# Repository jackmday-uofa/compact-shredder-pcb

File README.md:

# compact-shredder-pcb
PCB schematic and design for the Compact Shredder Design Version 2

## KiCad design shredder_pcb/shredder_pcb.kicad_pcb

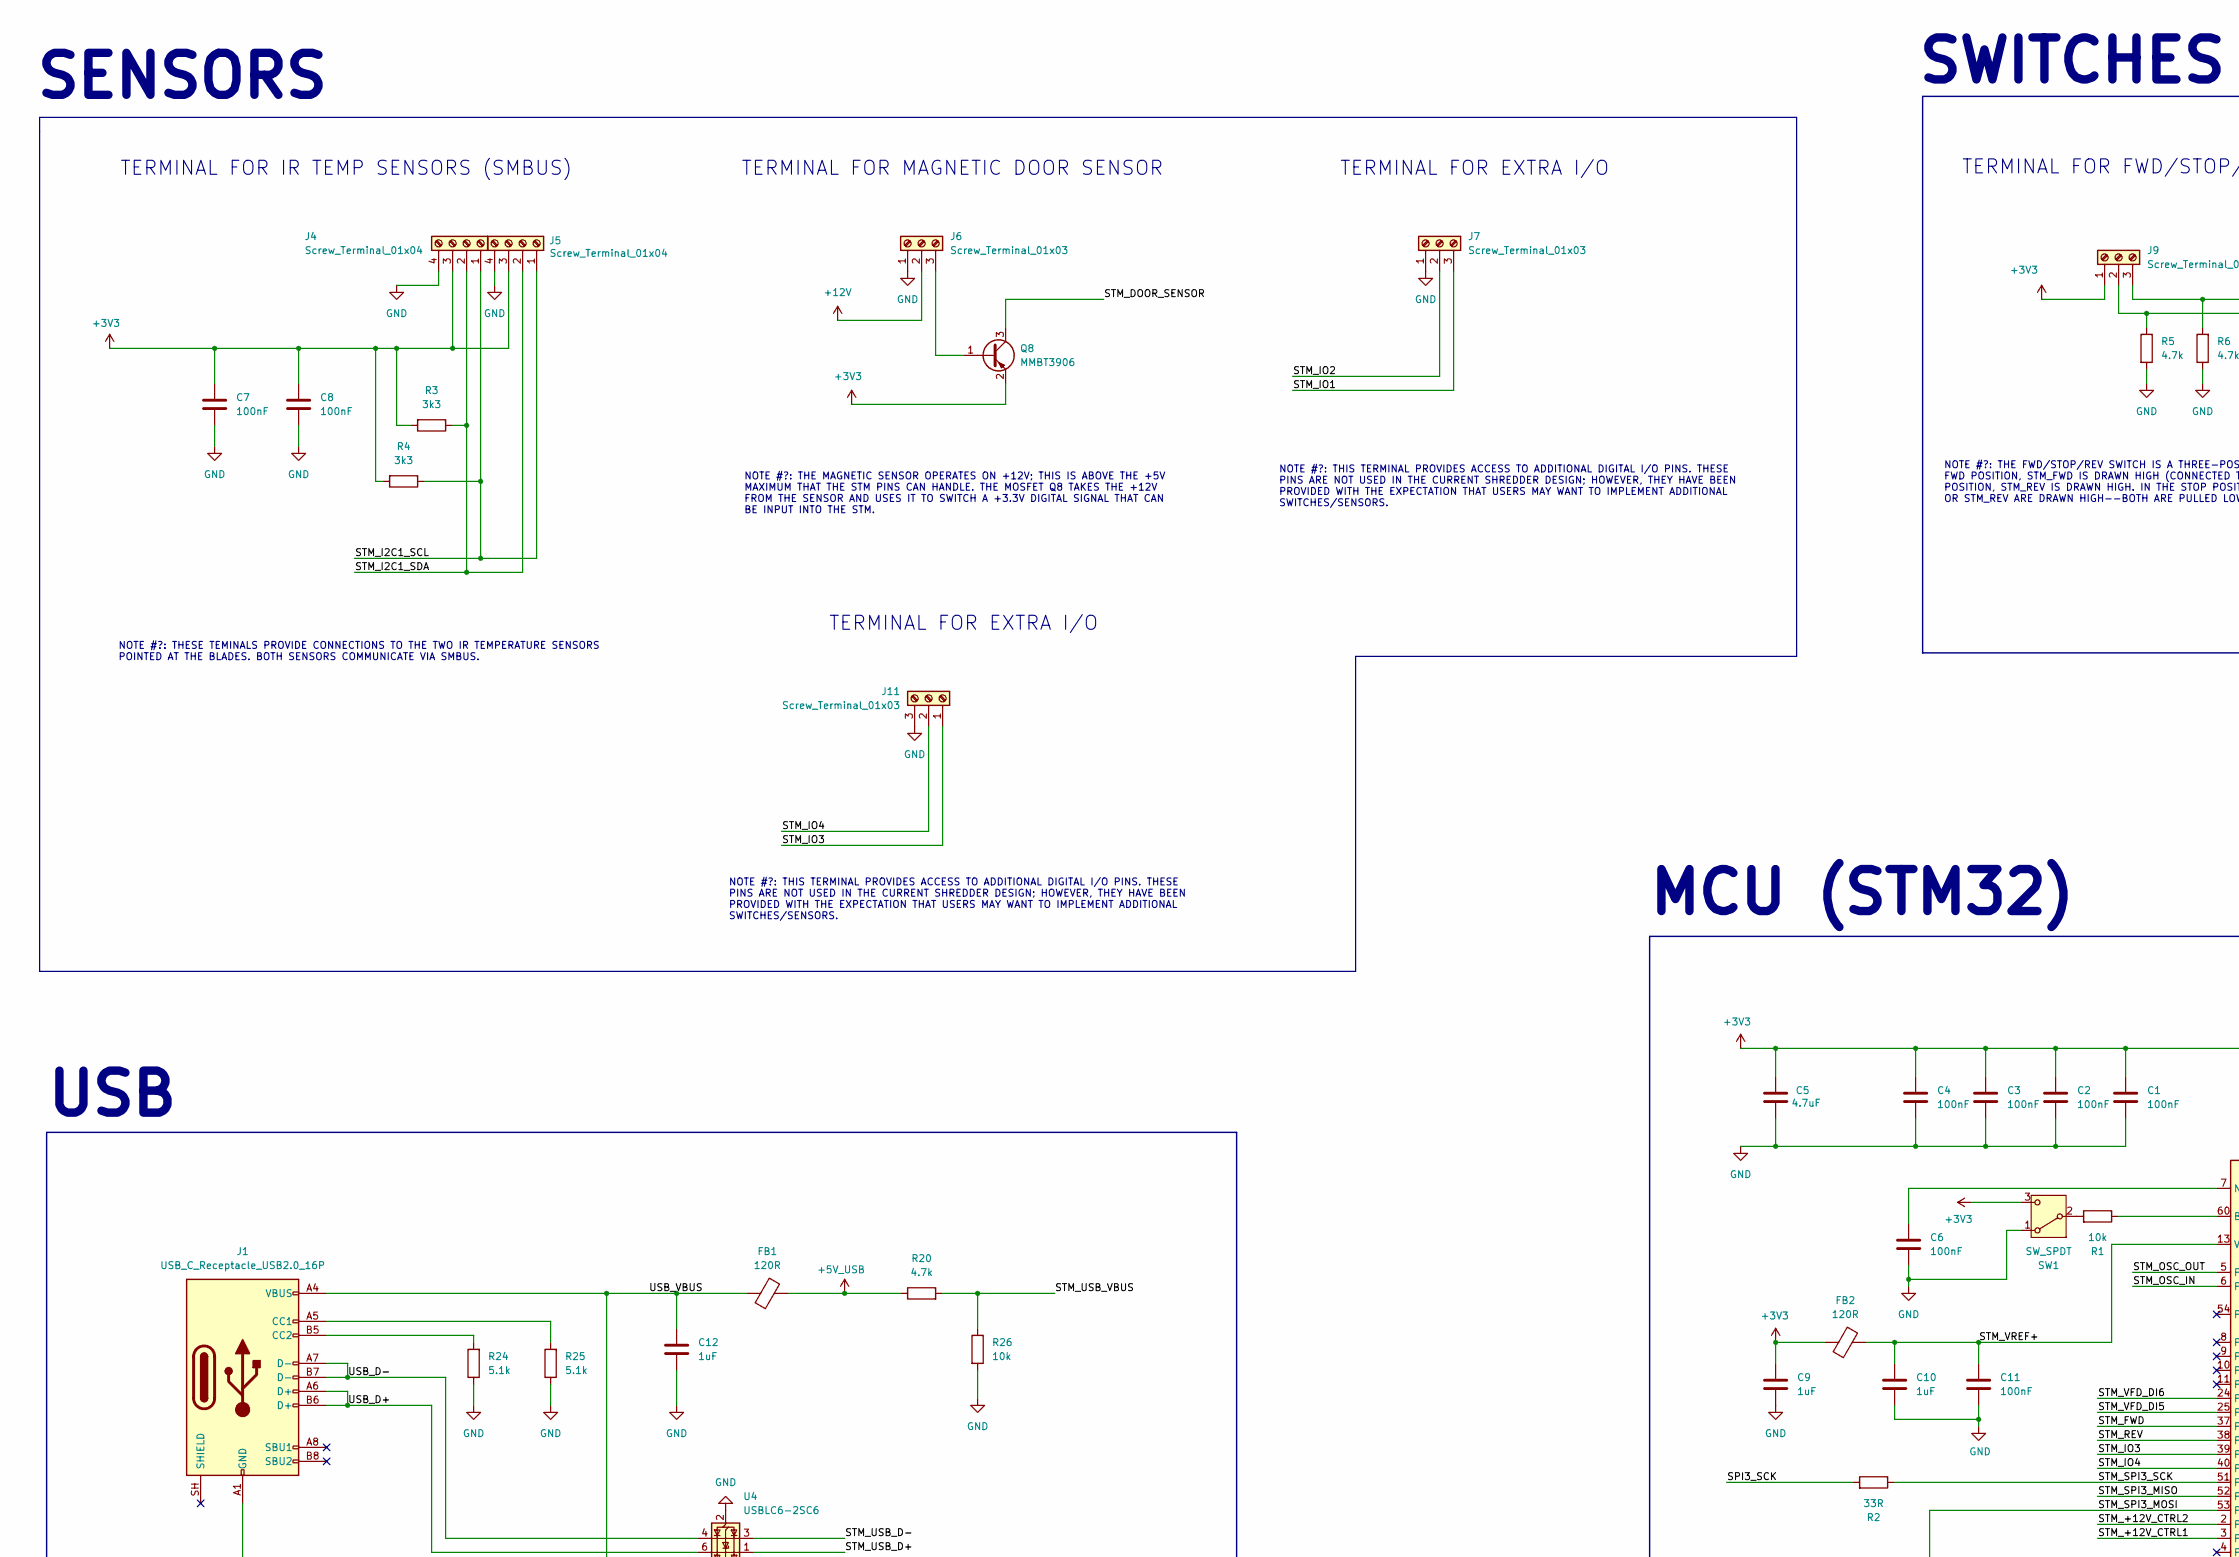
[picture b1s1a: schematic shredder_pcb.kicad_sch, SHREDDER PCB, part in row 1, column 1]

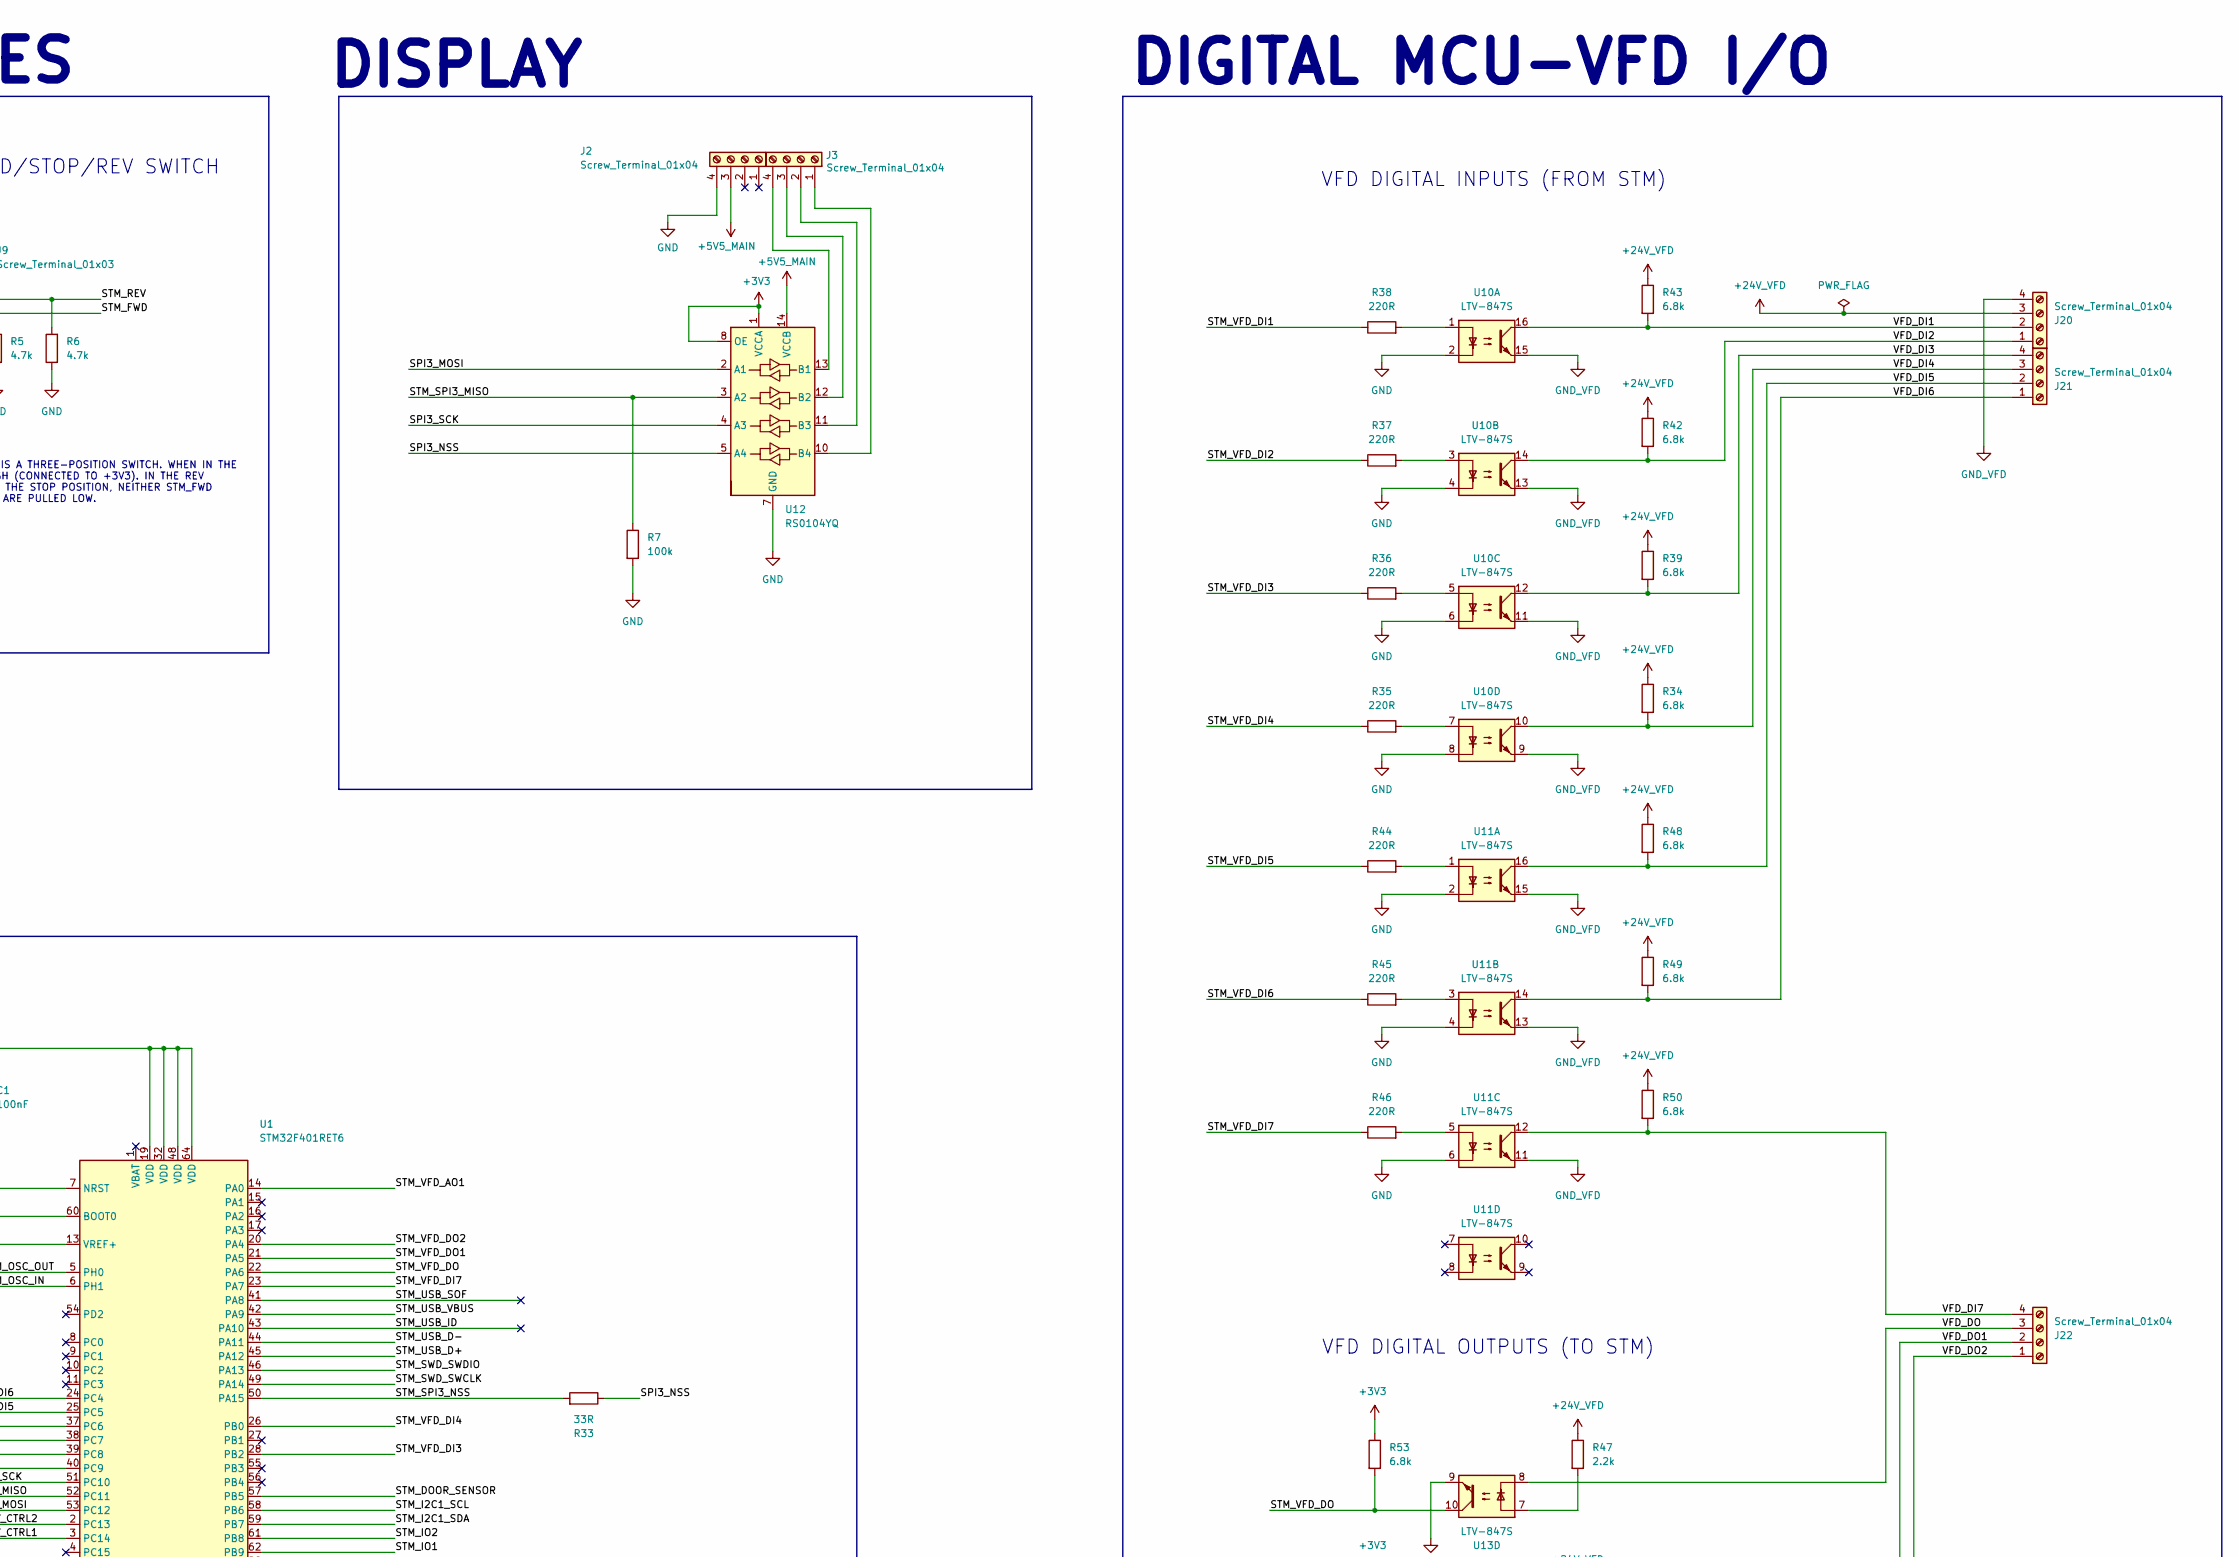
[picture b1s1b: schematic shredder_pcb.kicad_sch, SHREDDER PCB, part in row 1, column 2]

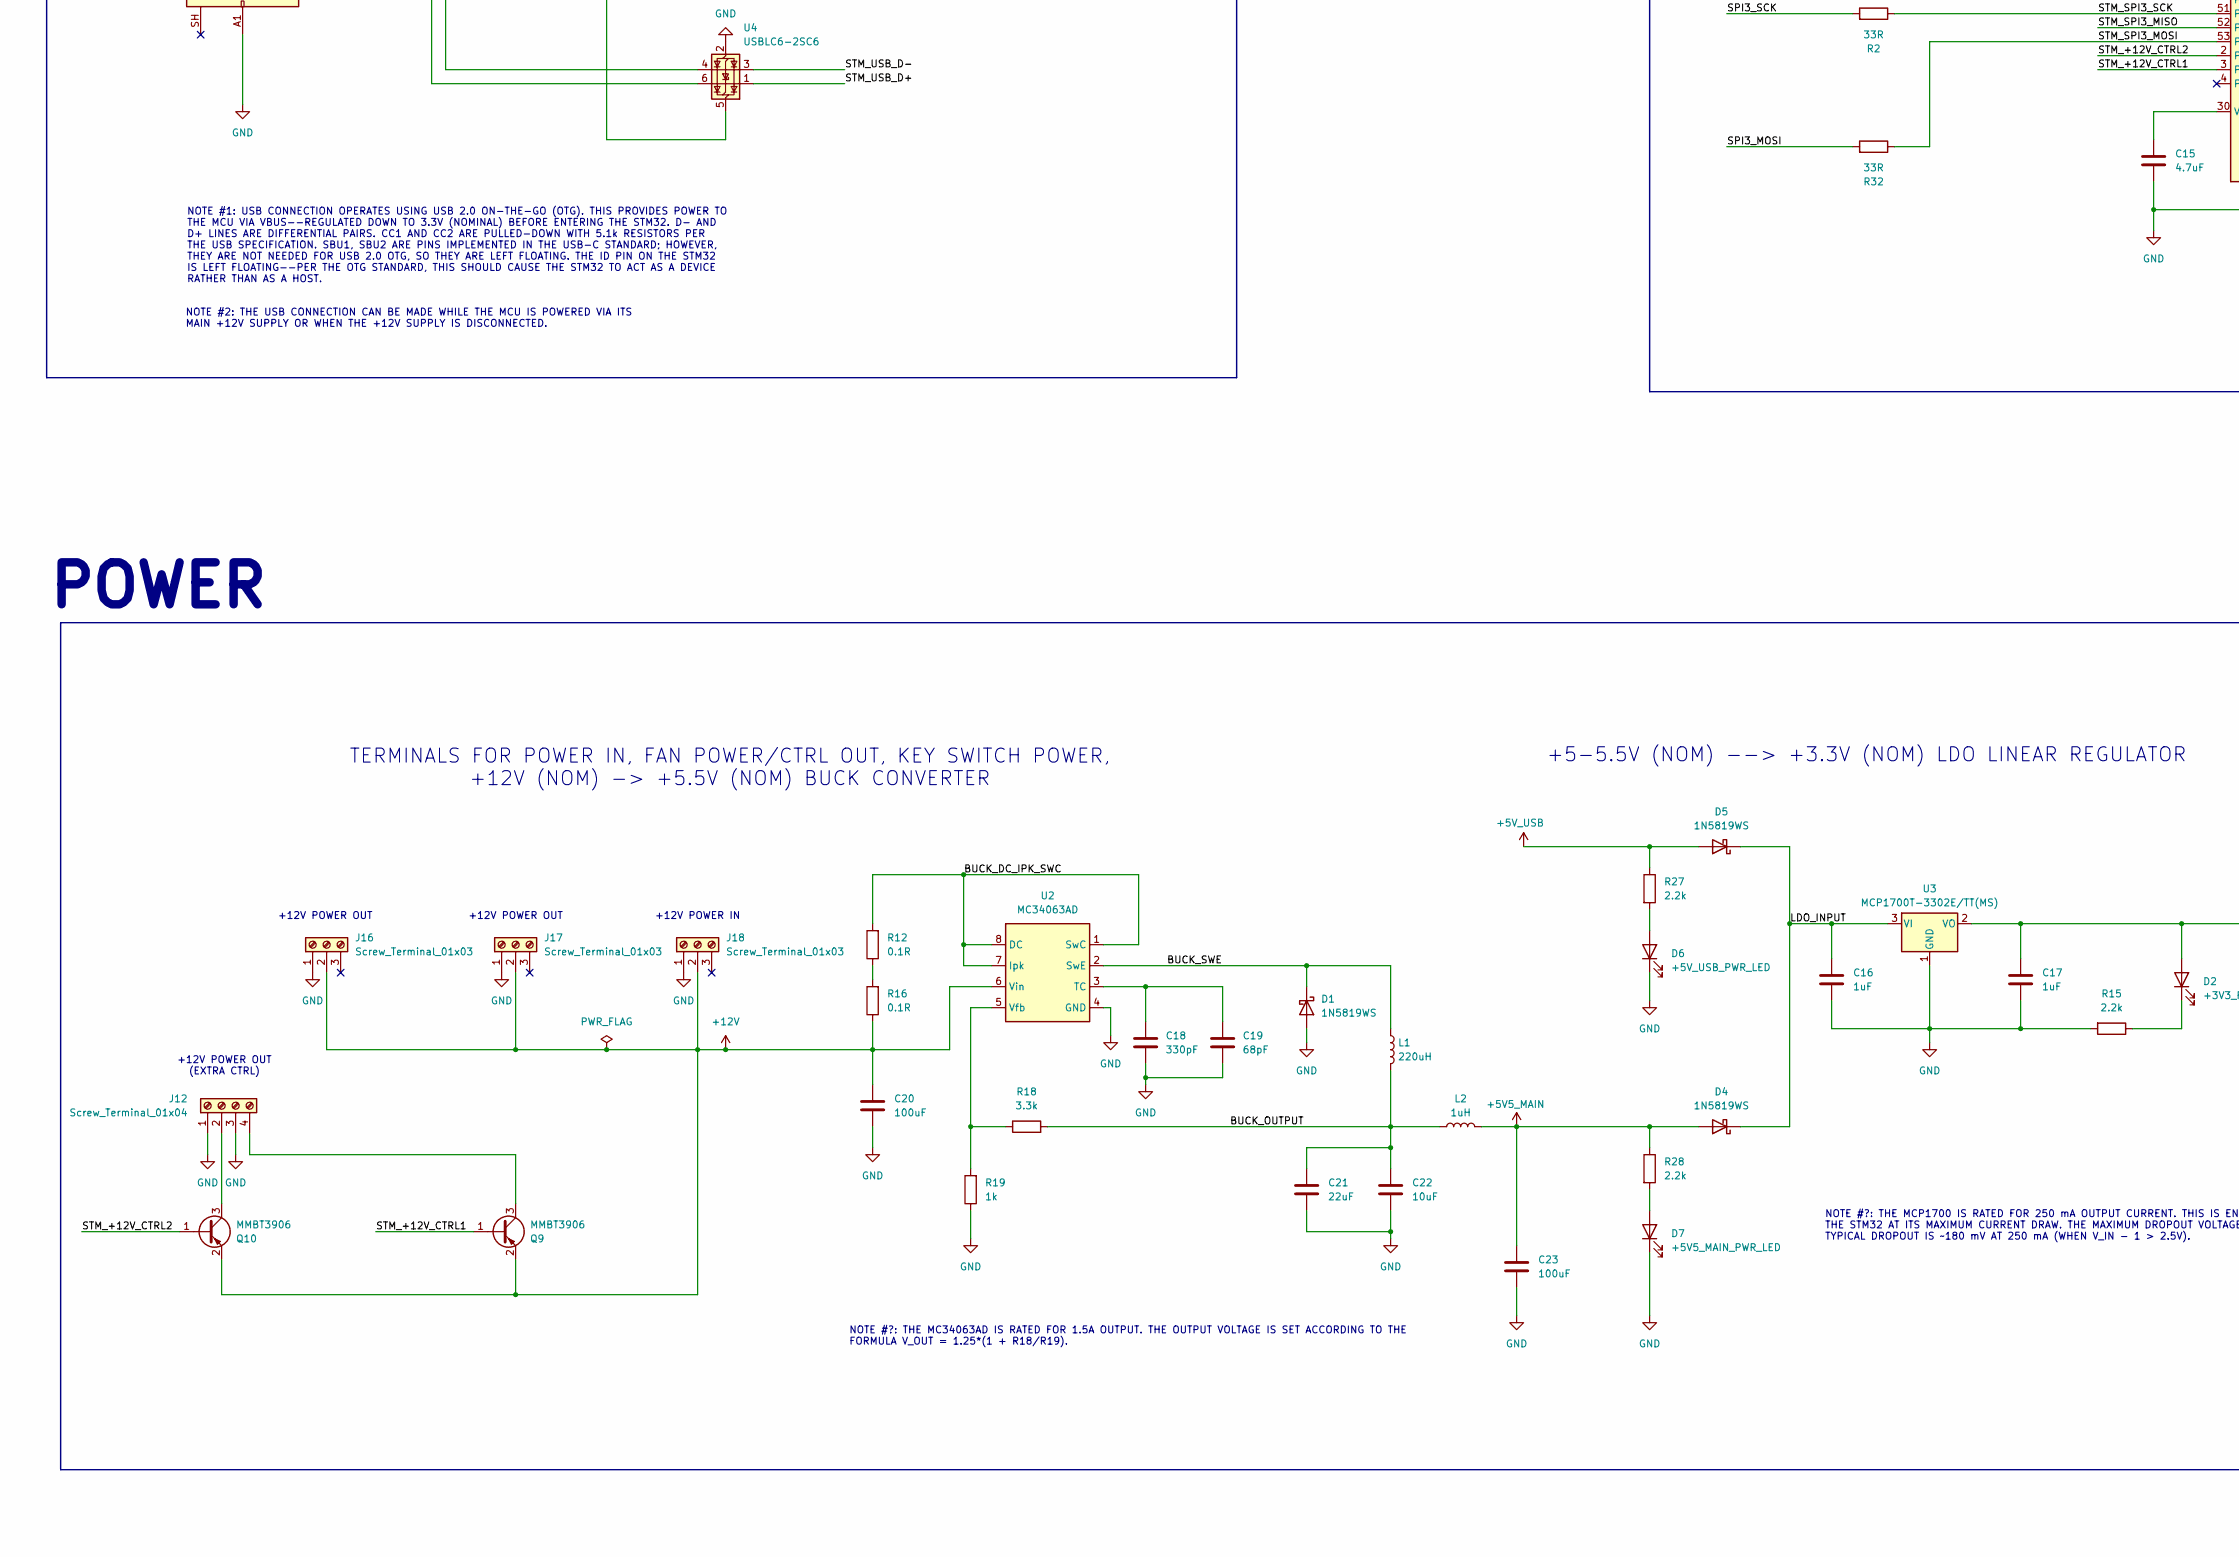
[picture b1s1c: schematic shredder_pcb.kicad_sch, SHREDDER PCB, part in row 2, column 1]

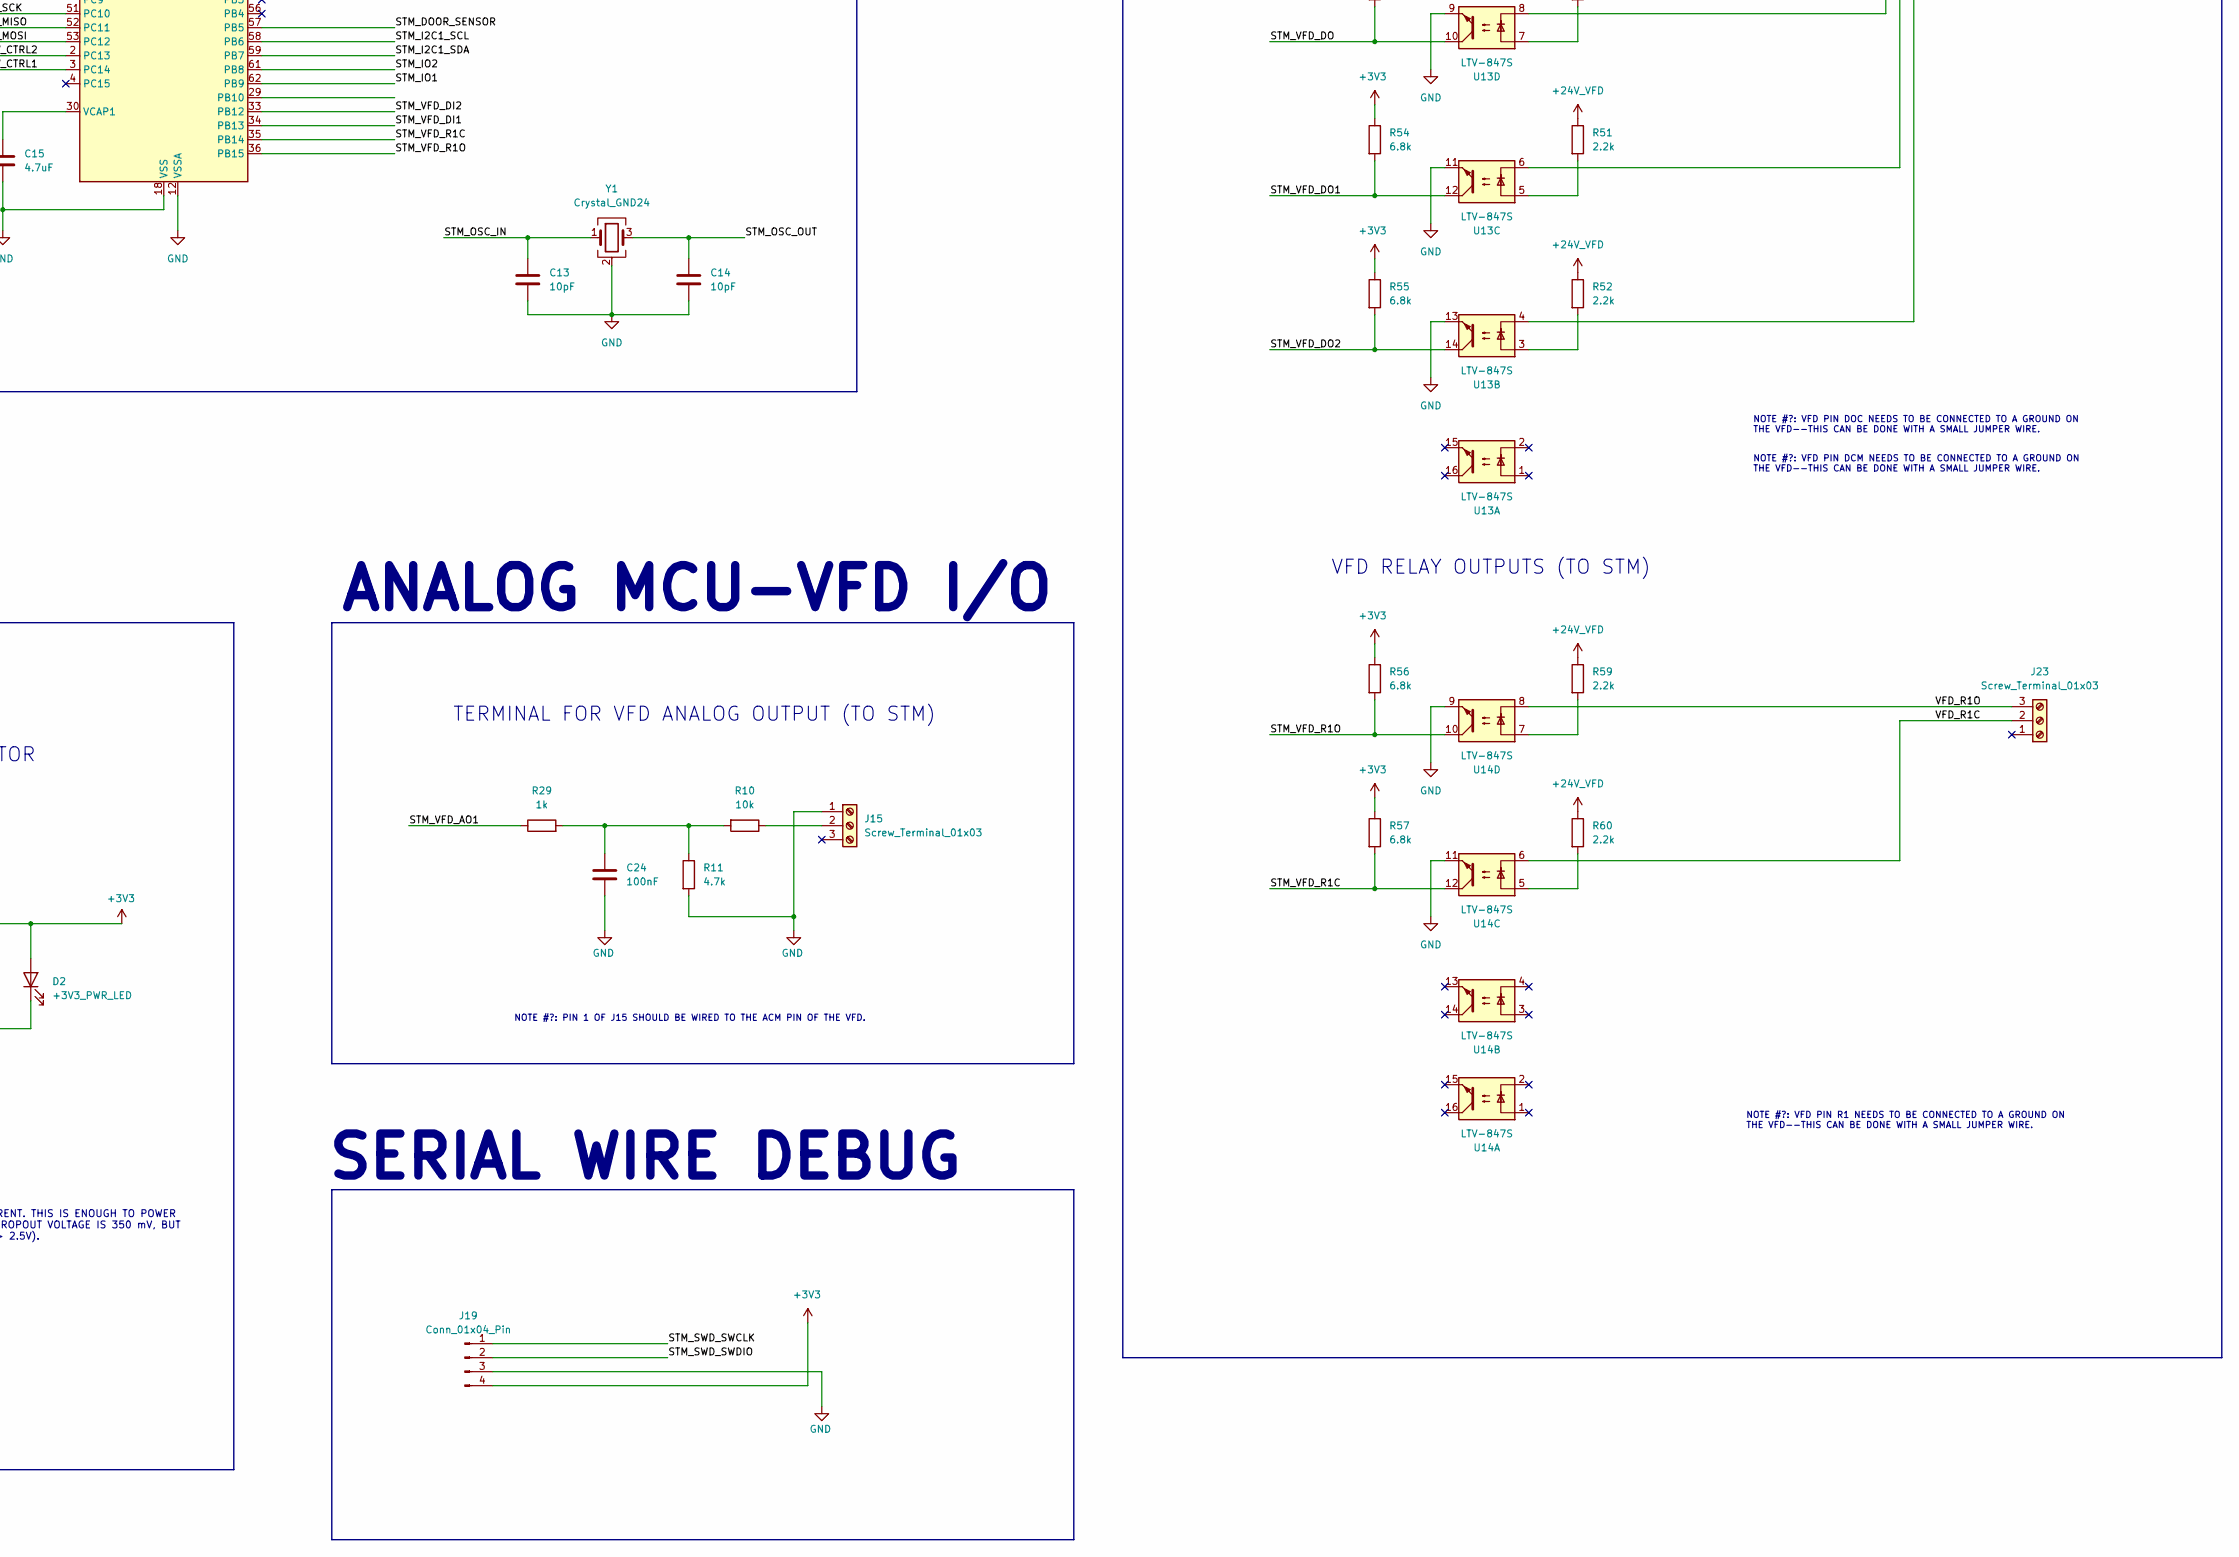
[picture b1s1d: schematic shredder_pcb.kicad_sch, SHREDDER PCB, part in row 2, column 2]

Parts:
C1, C2, C3, C4, C6, C7, C8, C11, C24: 100nF; C_0805_2012Metric
C5, C15: 4.7uF; C_0805_2012Metric
C9, C10, C12, C16, C17: 1uF; C_0805_2012Metric
C13, C14: 10pF; C_0603_1608Metric
C18: 330pF; C_0603_1608Metric
C19: 68pF; C_0603_1608Metric
C20, C23: 100uF; C_1206_3216Metric
C21: 22uF; C_1206_3216Metric
C22: 10uF; C_0805_2012Metric
D1, D4, D5: 1N5819WS; D_SOD-323
D2: +3V3_PWR_LED; LED_0603_1608Metric
D6: +5V_USB_PWR_LED; LED_0603_1608Metric
D7: +5V5_MAIN_PWR_LED; LED_0603_1608Metric
FB1, FB2: 120R; L_0805_2012Metric
J1: USB_C_Receptacle_USB2.0_16P; USB_C_Receptacle_GCT_USB4110
J2, J3, J4, J5, J12, J20, J21, J22: Screw_Terminal_01x04; DB301V-5.0_1x4P
J6, J7, J9, J11, J15, J16, J17, J18, J23: Screw_Terminal_01x03; KF301-5.0_1x3P
J19: Conn_01x04_Pin; PinHeader_1x04_P2.54mm_Vertical
L1: 220uH; L_1210_3225Metric
L2: 1uH; L_0805_2012Metric
Q8, Q9, Q10: MMBT3906; SOT-23-3
R1, R10, R26: 10k; R_0603_1608Metric
R2, R32, R33: 33R; R_0805_2012Metric
R3, R4: 3k3; R_0603_1608Metric
R5, R6, R11, R20: 4.7k; R_0603_1608Metric
R7: 100k; R_0603_1608Metric
R12, R16: 0.1R; R_1206_3216Metric
R15, R27, R28, R47, R51, R52, R59, R60: 2.2k; R_0603_1608Metric
R18: 3.3k; R_0603_1608Metric
R19, R29: 1k; R_0603_1608Metric
R24, R25: 5.1k; R_1206_3216Metric
R34, R39, R42, R43, R48, R49, R50, R53, R54, R55, R56, R57: 6.8k; R_0603_1608Metric
R35, R36, R37, R38, R44, R45, R46: 220R; R_0603_1608Metric
SW1: SW_SPDT; SW_SPDT_Shouhan_MSK12C02
U1: STM32F401RET6; LQFP-64_10x10mm_P0.5mm
U2: MC34063AD; SOIC-8_3.9x4.9mm_P1.27mm
U3: MCP1700T-3302E/TT(MS); SOT-23
U4: USBLC6-2SC6; SOT-23-6
U10, U11, U13, U14: LTV-847S; SMDIP-16_W9.53mm
U12: RS0104YQ; TSSOP-14_4.4x5mm_P0.65mm
Y1: Crystal_GND24; Crystal_SMD_3225-4Pin_3.2x2.5mm

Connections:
+3V3: C1.1, C2.1, C3.1, C4.1, C5.1, C7.1, C8.1, C9.1, C17.1, D2.2 (A), FB2.1, J4.3, J5.3, J9.1, J19.4, Q8.2 (E), R3.2, R4.2, R53.1, R54.1, R55.1, R56.1, R57.1, SW1.3 (C), U1.19 (VDD), U1.32 (VDD), U1.48 (VDD), U1.64 (VDD), U3.2 (VO), U12.1 (VCCA), U12.8 (OE)
+5V5_MAIN: C23.2, D4.2 (A), J2.3, L2.2, R28.1, U12.14 (VCCB)
+5V_USB: D5.2 (A), FB1.2, R20.1, R27.1
+12V: C20.2, J6.2, J16.2, J17.2, J18.2, Q9.2 (E), Q10.2 (E), R16.1, U2.6 (Vin)
+24V_VFD: J20.3, R34.1, R39.1, R42.1, R43.1, R47.1, R48.1, R49.1, R50.1, R51.1, R52.1, R59.1, R60.1
/Root/BUCK_DC_IPK_SWC: R12.2, U2.1 (SwC), U2.7 (Ipk), U2.8 (DC)
/Root/BUCK_OUTPUT: C21.2, C22.2, L1.2, L2.1, R18.2
/Root/BUCK_SWE: D1.1 (K), L1.1, U2.2 (SwE)
/Root/LDO_INPUT: C16.1, D4.1 (K), D5.1 (K), U3.3 (VI)
/Root/SPI3_MOSI: R32.2, U12.2 (A1)
/Root/SPI3_NSS: R33.1, U12.5 (A4)
/Root/SPI3_SCK: R2.2, U12.4 (A3)
/Root/STM_+12V_CTRL1: Q9.1 (B), U1.3 (PC14)
/Root/STM_+12V_CTRL2: Q10.1 (B), U1.2 (PC13)
/Root/STM_DOOR_SENSOR: Q8.3 (C), U1.57 (PB5)
/Root/STM_FWD: J9.2, R5.1, U1.37 (PC6)
/Root/STM_I2C1_SCL: J4.1, J5.1, R4.1, U1.58 (PB6)
/Root/STM_I2C1_SDA: J4.2, J5.2, R3.1, U1.59 (PB7)
/Root/STM_IO1: J7.3, U1.62 (PB9)
/Root/STM_IO2: J7.2, U1.61 (PB8)
/Root/STM_IO3: J11.1, U1.39 (PC8)
/Root/STM_IO4: J11.2, U1.40 (PC9)
/Root/STM_OSC_IN: C13.1, U1.6 (PH1), Y1.1
/Root/STM_OSC_OUT: C14.1, U1.5 (PH0), Y1.3
/Root/STM_REV: J9.3, R6.2, U1.38 (PC7)
/Root/STM_SPI3_MISO: R7.1, U1.52 (PC11), U12.3 (A2)
/Root/STM_SPI3_MOSI: R32.1, U1.53 (PC12)
/Root/STM_SPI3_NSS: R33.2, U1.50 (PA15)
/Root/STM_SPI3_SCK: R2.1, U1.51 (PC10)
/Root/STM_SWD_SWCLK: J19.1, U1.49 (PA14)
/Root/STM_SWD_SWDIO: J19.2, U1.46 (PA13)
/Root/STM_USB_D+: U1.45 (PA12), U4.1 (I/O1)
/Root/STM_USB_D-: U1.44 (PA11), U4.3 (I/O2)
/Root/STM_USB_ID: U1.43 (PA10)
/Root/STM_USB_SOF: U1.41 (PA8)
/Root/STM_USB_VBUS: R20.2, R26.1, U1.42 (PA9)
/Root/STM_VFD_AO1: R29.1, U1.14 (PA0)
/Root/STM_VFD_DI1: R38.1, U1.34 (PB13)
/Root/STM_VFD_DI2: R37.1, U1.33 (PB12)
/Root/STM_VFD_DI3: R36.1, U1.28 (PB2)
/Root/STM_VFD_DI4: R35.1, U1.26 (PB0)
/Root/STM_VFD_DI5: R44.1, U1.25 (PC5)
/Root/STM_VFD_DI6: R45.1, U1.24 (PC4)
/Root/STM_VFD_DI7: R46.1, U1.23 (PA7)
/Root/STM_VFD_DO: R53.2, U1.22 (PA6), U13.10
/Root/STM_VFD_DO1: R54.2, U1.21 (PA5), U13.12
/Root/STM_VFD_DO2: R55.2, U1.20 (PA4), U13.14
/Root/STM_VFD_R1C: R57.2, U1.35 (PB14), U14.12
/Root/STM_VFD_R1O: R56.2, U1.36 (PB15), U14.10
/Root/STM_VREF+: C10.1, C11.1, FB2.2, U1.13 (VREF+)
/Root/USB_D+: J1.A6 (D+), J1.B6 (D+), U4.6 (I/O1)
/Root/USB_D-: J1.A7 (D-), J1.B7 (D-), U4.4 (I/O2)
/Root/USB_VBUS: C12.1, FB1.1, J1.A4 (VBUS), J1.A9 (VBUS), J1.B4 (VBUS), J1.B9 (VBUS), U4.5 (VBUS)
/Root/VFD_DI1: J20.2, R43.2, U10.16
/Root/VFD_DI2: J20.1, R42.2, U10.14
/Root/VFD_DI3: J21.4, R39.2, U10.12
/Root/VFD_DI4: J21.3, R34.2, U10.10
/Root/VFD_DI5: J21.2, R48.2, U11.16
/Root/VFD_DI6: J21.1, R49.2, U11.14
/Root/VFD_DI7: J22.4, R50.2, U11.12
/Root/VFD_DO: J22.3, U13.8
/Root/VFD_DO1: J22.2, U13.6
/Root/VFD_DO2: J22.1, U13.4
/Root/VFD_R1C: J23.2, U14.6
/Root/VFD_R1O: J23.3, U14.8
GND: C1.2, C2.2, C3.2, C4.2, C5.2, C6.2, C7.2, C8.2, C9.2, C10.2, C11.2, C12.2, C13.2, C14.2, C15.2, C16.2, C17.2, C18.1, C19.1, C20.1, C21.1, C22.1, C23.1, C24.2, D1.2 (A), D6.1 (K), D7.1 (K), J1.A1 (GND), J1.A12 (GND), J1.B1 (GND), J1.B12 (GND), J2.4, J4.4, J5.4, J6.1, J7.1, J11.3, J12.1, J12.3, J15.1, J16.1, J17.1, J18.1, J19.3, R5.2, R6.1, R7.2, R11.2, R15.2, R19.1, R24.1, R25.1, R26.2, SW1.1 (A), U1.12 (VSSA), U1.18 (VSS), U1.31 (VSS), U1.47 (VSS), U1.63 (VSS), U2.4 (GND), U3.1 (GND), U4.2 (GND), U10.2, U10.4, U10.6, U10.8, U11.2, U11.4, U11.6, U12.7 (GND), U13.9, U13.11, U13.13, U14.9, U14.11, Y1.2 (G), Y1.4 (G)
GND_VFD: J20.4, U10.9, U10.11, U10.13, U10.15, U11.11, U11.13, U11.15
unnamed: C24.1, R10.2, R11.1, R29.2
unnamed: D2.1 (K), R15.1
unnamed: D6.2 (A), R27.2
unnamed: D7.2 (A), R28.2
unnamed: J1.A5 (CC1), R25.2
unnamed: J1.B5 (CC2), R24.2
unnamed: J3.1, U12.10 (B4)
unnamed: J3.2, U12.11 (B3)
unnamed: J3.3, U12.12 (B2)
unnamed: J3.4, U12.13 (B1)
unnamed: J6.3, Q8.1 (B)
unnamed: J12.2, Q10.3 (C)
unnamed: J12.4, Q9.3 (C)
unnamed: J15.2, R10.1
unnamed: R12.1, R16.2
unnamed: R35.2, U10.7
unnamed: R36.2, U10.5
unnamed: R37.2, U10.3
unnamed: R38.2, U10.1
unnamed: R44.2, U11.1
unnamed: R45.2, U11.3
unnamed: R46.2, U11.5
unnamed: R47.2, U13.7
unnamed: R51.2, U13.5
unnamed: R52.2, U13.3
unnamed: R59.2, U14.7
unnamed: R60.2, U14.5
unnamed: R1.2, SW1.2 (B)
unnamed: R1.1, U1.60 (BOOT0)
unnamed: C6.1, U1.7 (NRST)
unnamed: C15.1, U1.30 (VCAP1)
unnamed: C18.2, C19.2, U2.3 (TC)
unnamed: R18.1, R19.2, U2.5 (Vfb)

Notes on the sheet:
+12V POWER IN
TERMINAL FOR EXTRA I/O
VFD DIGITAL OUTPUTS (TO STM)
DIGITAL MCU-VFD I/O
TERMINAL FOR MAGNETIC DOOR SENSOR
+5-5.5V (NOM) --> +3.3V (NOM) LDO LINEAR REGULATOR
NOTE #?: THESE TEMINALS PROVIDE CONNECTIONS TO THE TWO IR TEMPERATURE SENSORS POINTED AT THE BLADES. BOTH SENSORS COMMUNICATE VIA SMBUS.
SERIAL WIRE DEBUG
TERMINAL FOR VFD ANALOG OUTPUT (TO STM)
+12V POWER OUT
VFD RELAY OUTPUTS (TO STM)
NOTE #?: THE MAGNETIC SENSOR OPERATES ON +12V; THIS IS ABOVE THE +5V MAXIMUM THAT THE STM PINS CAN HANDLE. THE MOSFET Q8 TAKES THE +12V FROM THE SENSOR AND USES IT TO SWITCH A +3.3V DIGITAL SIGNAL THAT CAN BE INPUT INTO THE STM.
NOTE #?: VFD PIN DOC NEEDS TO BE CONNECTED TO A GROUND ON THE VFD--THIS CAN BE DONE WITH A SMALL JUMPER WIRE.
SENSORS
TERMINALS FOR POWER IN, FAN POWER/CTRL OUT, KEY SWITCH POWER, +12V (NOM) -> +5.5V (NOM) BUCK CONVERTER
MCU (STM32)
NOTE #?: THIS TERMINAL PROVIDES ACCESS TO ADDITIONAL DIGITAL I/O PINS. THESE PINS ARE NOT USED IN THE CURRENT SHREDDER DESIGN; HOWEVER, THEY HAVE BEEN PROVIDED WITH THE EXPECTATION THAT USERS MAY WANT TO IMPLEMENT ADDITIONAL SWITCHES/SENSORS.
ANALOG MCU-VFD I/O
NOTE #2: THE USB CONNECTION CAN BE MADE WHILE THE MCU IS POWERED VIA ITS MAIN +12V SUPPLY OR WHEN THE +12V SUPPLY IS DISCONNECTED.
DISPLAY
NOTE #?: VFD PIN R1 NEEDS TO BE CONNECTED TO A GROUND ON THE VFD--THIS CAN BE DONE WITH A SMALL JUMPER WIRE.
TERMINAL FOR FWD/STOP/REV SWITCH
USB
NOTE #1: USB CONNECTION OPERATES USING USB 2.0 ON-THE-GO (OTG). THIS PROVIDES POWER TO THE MCU VIA VBUS--REGULATED DOWN TO 3.3V (NOMINAL) BEFORE ENTERING THE STM32. D- AND D+ LINES ARE DIFFERENTIAL PAIRS. CC1 AND CC2 ARE PULLED-DOWN WITH 5.1k RESISTORS PER THE USB SPECIFICATION. SBU1, SBU2 ARE PINS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
VFD DIGITAL INPUTS (FROM STM)
NOTE #?: VFD PIN DCM NEEDS TO BE CONNECTED TO A GROUND ON THE VFD--THIS CAN BE DONE WITH A SMALL JUMPER WIRE.
+12V POWER OUT (EXTRA CTRL)
NOTE #?: THE FWD/STOP/REV SWITCH IS A THREE-POSITION SWITCH. WHEN IN THE FWD POSITION, STM_FWD IS DRAWN HIGH (CONNECTED TO +3V3). IN THE REV POSITION, STM_REV IS DRAWN HIGH. IN THE STOP POSITION, NEITHER STM_FWD OR STM_REV ARE DRAWN HIGH--BOTH ARE PULLED LOW.
NOTE #?: THE MC34063AD IS RATED FOR 1.5A OUTPUT. THE OUTPUT VOLTAGE IS SET ACCORDING TO THE FORMULA V_OUT = 1.25*(1 + R18/R19).
NOTE #?: PIN 1 OF J15 SHOULD BE WIRED TO THE ACM PIN OF THE VFD.
SWITCHES
POWER
TERMINAL FOR IR TEMP SENSORS (SMBUS)
NOTE #?: THE MCP1700 IS RATED FOR 250 mA OUTPUT CURRENT. THIS IS ENOUGH TO POWER THE STM32 AT ITS MAXIMUM CURRENT DRAW. THE MAXIMUM DROPOUT VOLTAGE IS 350 mV, BUT TYPICAL DROPOUT IS ~180 mV AT 250 mA (WHEN V_IN - 1 > 2.5V).

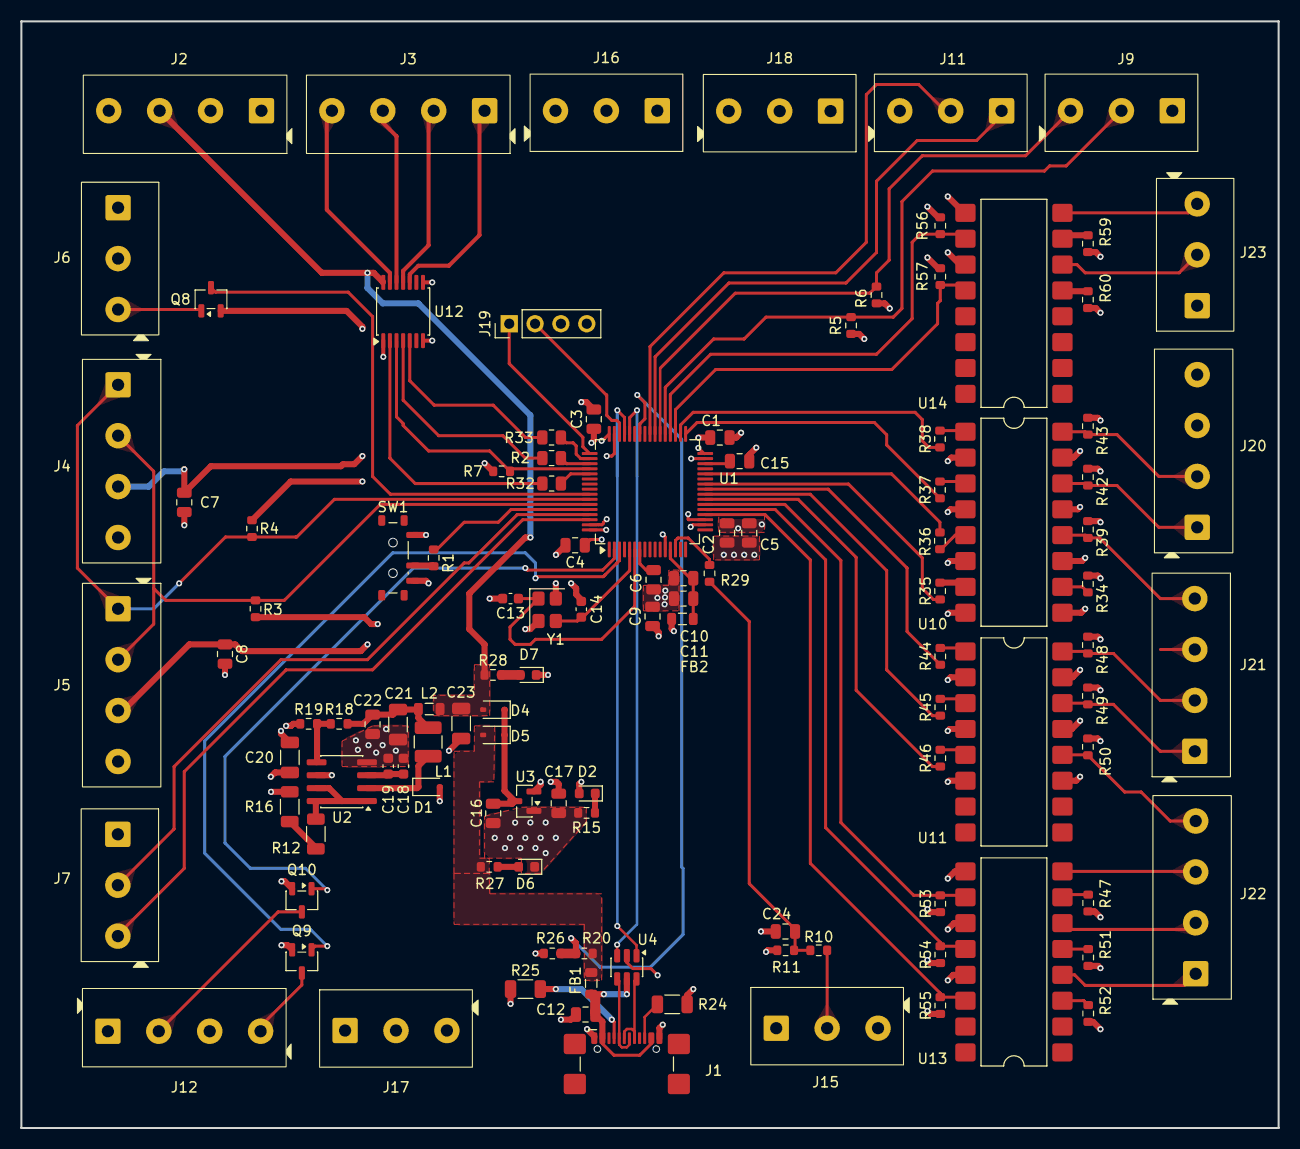
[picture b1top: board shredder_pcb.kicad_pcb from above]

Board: 4 copper layers, 123.5 x 108.7 mm, 114 parts (0 on the bottom side), 98 nets.

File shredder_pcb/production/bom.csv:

Designator,Footprint,Quantity,Value,LCSC Part #
"C1, C11, C2, C24, C3, C4, C6, C7, C8",0805,9,100nF,
"C10, C12, C16, C17, C9",0805,5,1uF,
"C13, C14",0603,2,10pF,
"C15, C5",0805,2,4.7uF,
C18,0603,1,330pF,
C19,0603,1,68pF,
"C20, C23",1206,2,100uF,
C21,1206,1,22uF,
C22,0805,1,10uF,
"D1, D4, D5",D_SOD-323,3,1N5819WS,
D2,0603,1,+3V3_PWR_LED,
D6,0603,1,+5V_USB_PWR_LED,
D7,0603,1,+5V5_MAIN_PWR_LED,
"FB1, FB2",0805,2,120R,
J1,USB_C_Receptacle_GCT_USB4110,1,USB_C_Receptacle_USB2.0_16P,
"J11, J15, J16, J17, J18, J23, J6, J7, J9",KF301-5.0_1x3P,9,Screw_Terminal_01x03,
"J12, J2, J20, J21, J22, J3, J4, J5",DB301V-5.0_1x4P,8,Screw_Terminal_01x04,
J19,PinHeader_1x04_P2.54mm_Vertical,1,Conn_01x04_Pin,
L1,1210,1,220uH,
L2,0805,1,1uH,
"Q10, Q8, Q9",SOT-23-3,3,MMBT3906,
"R1, R10, R26",0603,3,10k,
"R11, R20, R5, R6",0603,4,4.7k,
"R12, R16",1206,2,0.1R,
"R15, R27, R28, R47, R51, R52, R59, R60",0603,8,2.2k,
R18,0603,1,3.3k,
"R19, R29",0603,2,1k,
"R2, R32, R33",0805,3,33R,
"R24, R25",1206,2,5.1k,
"R3, R4",0603,2,3k3,
"R34, R39, R42, R43, R48, R49, R50, R53, R54, R55, R56, R57",0603,12,6.8k,
"R35, R36, R37, R38, R44, R45, R46",0603,7,220R,
R7,0603,1,100k,
SW1,SW_SPDT_Shouhan_MSK12C02,1,SW_SPDT,
U1,LQFP-64_10x10mm_P0.5mm,1,STM32F401RET6,
"U10, U11, U13, U14",SMDIP-16_W9.53mm,4,LTV-847S,
U12,TSSOP-14_4.4x5mm_P0.65mm,1,RS0104YQ,
U2,SOIC-8_3.9x4.9mm_P1.27mm,1,MC34063AD,
U3,SOT-23,1,MCP1700T-3302E/TT(MS),
U4,SOT-23-6,1,USBLC6-2SC6,
Y1,Crystal_SMD_3225-4Pin_3.2x2.5mm,1,Crystal_GND24,

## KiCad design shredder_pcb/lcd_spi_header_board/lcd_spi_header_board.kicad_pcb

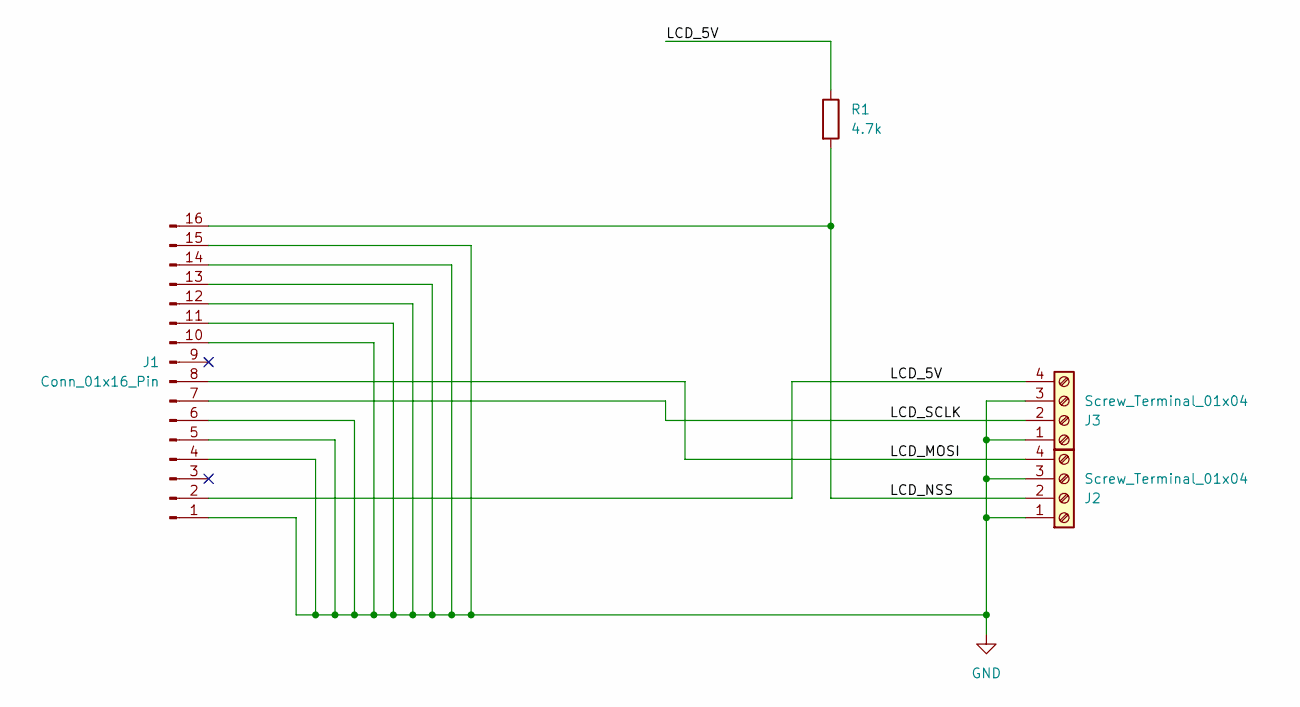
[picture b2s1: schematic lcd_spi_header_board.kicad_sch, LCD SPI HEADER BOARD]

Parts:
J1: Conn_01x16_Pin; PinSocket_1x16_P2.54mm_Vertical
J2, J3: Screw_Terminal_01x04; DB301V-5.0_1x4P
R1: 4.7k; R_0805_2012Metric

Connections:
/LCD_5V: J1.2, J3.4, R1.1
/LCD_MOSI: J1.8, J2.4
/LCD_NSS: J1.16, J2.2, R1.2
/LCD_SCLK: J1.7, J3.2
GND: J1.1, J1.4, J1.5, J1.6, J1.10, J1.11, J1.12, J1.13, J1.14, J1.15, J2.1, J2.3, J3.1, J3.3

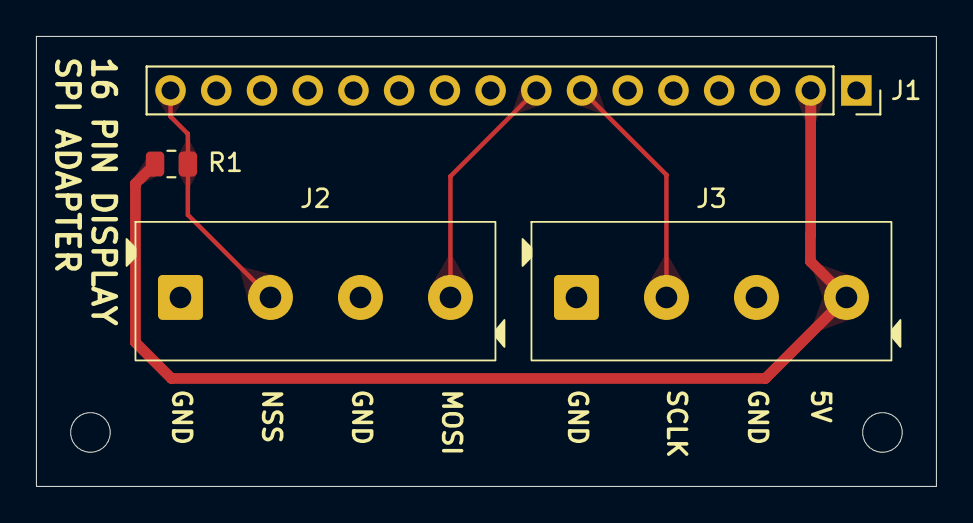
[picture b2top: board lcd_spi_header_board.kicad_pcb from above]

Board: 2 copper layers, 50.0 x 25.0 mm, 4 parts (0 on the bottom side), 5 nets.

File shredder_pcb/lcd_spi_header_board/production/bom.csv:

Designator,Footprint,Quantity,Value,LCSC Part #
J1,PinSocket_1x16_P2.54mm_Vertical,1,Conn_01x16_Pin,
"J2, J3",DB301V-5.0_1x4P,2,Screw_Terminal_01x04,
R1,0805,1,4.7k,
